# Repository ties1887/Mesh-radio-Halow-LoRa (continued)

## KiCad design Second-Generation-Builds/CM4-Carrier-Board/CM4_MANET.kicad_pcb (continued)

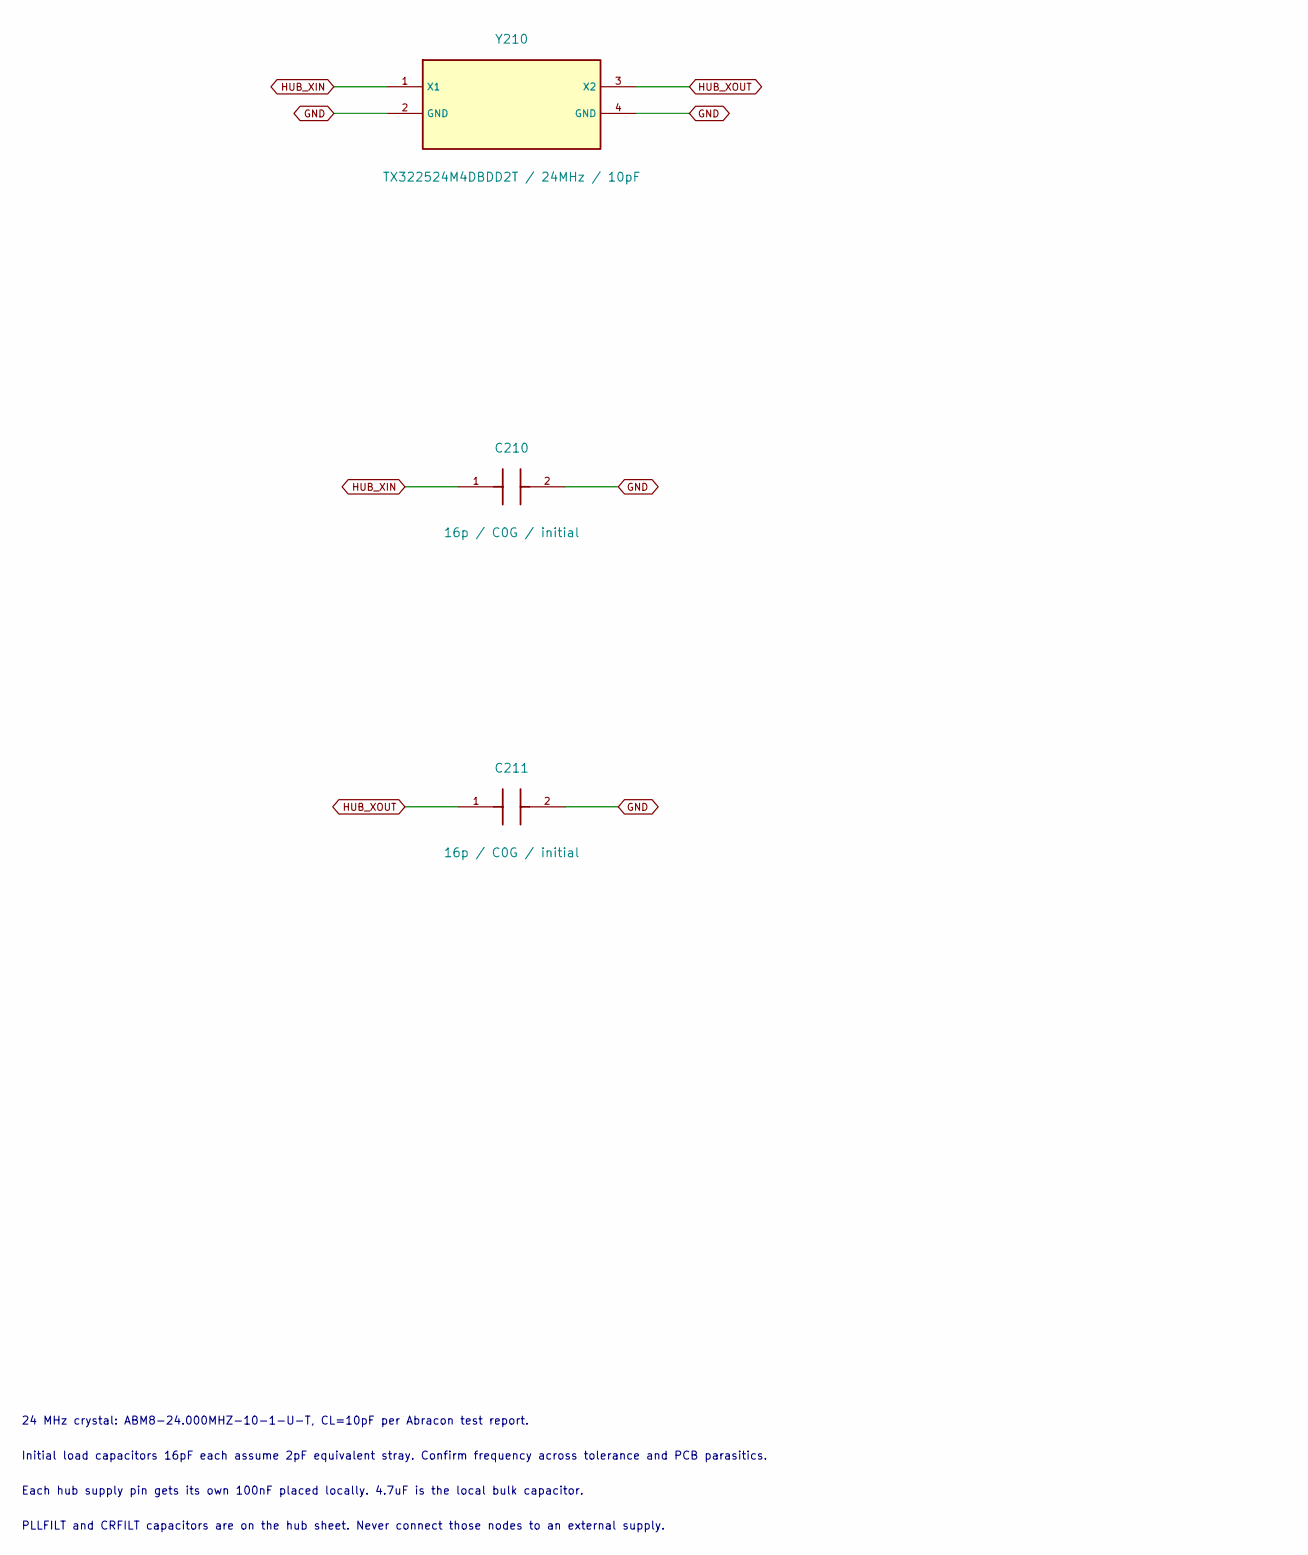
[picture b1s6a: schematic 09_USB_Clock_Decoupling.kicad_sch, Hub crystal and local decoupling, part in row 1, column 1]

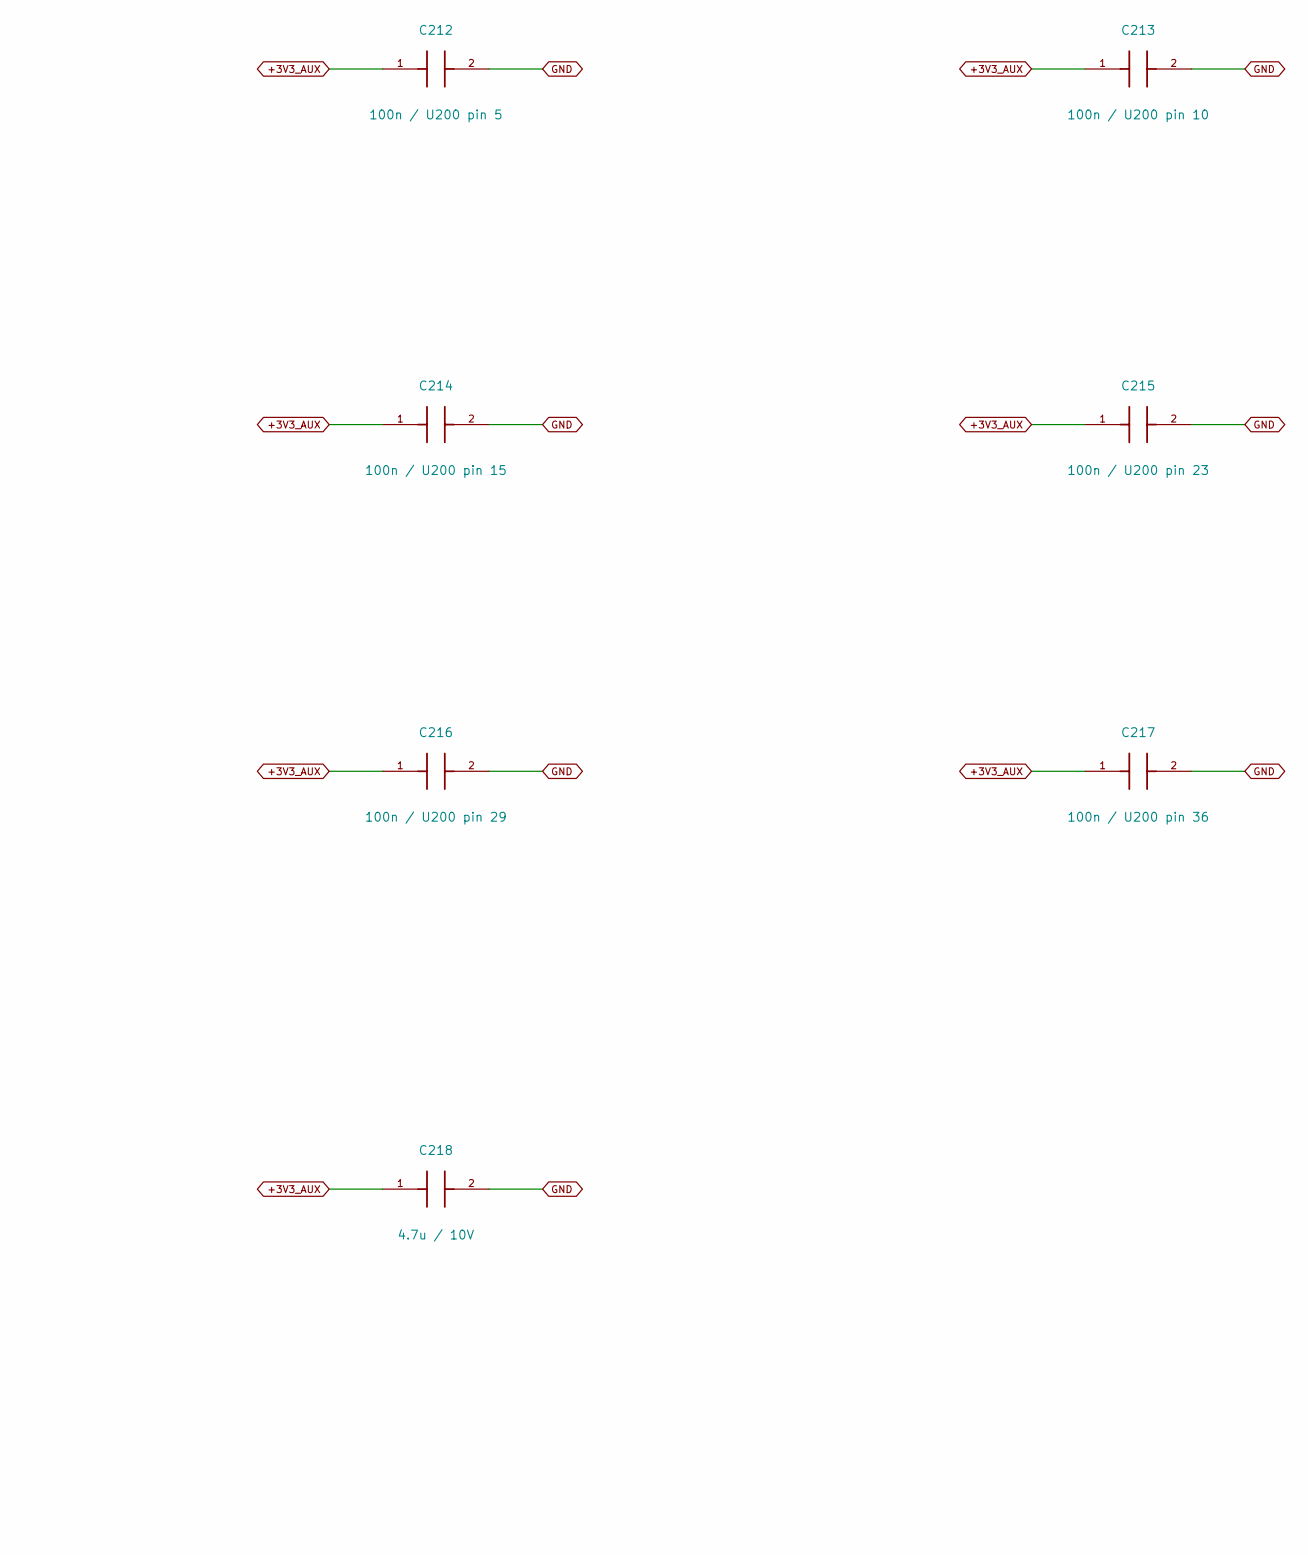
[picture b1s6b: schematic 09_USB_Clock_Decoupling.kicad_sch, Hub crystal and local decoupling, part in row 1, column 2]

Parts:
C210, C211: 16p / C0G / initial; C_0603_1608Metric; MPN CGA0603C0G160J500JT; LCSC C51704736
C212: 100n / U200 pin 5; C_0603_1608Metric; MPN CL10B104KB8NNNC; LCSC C1591
C213: 100n / U200 pin 10; C_0603_1608Metric; MPN CL10B104KB8NNNC; LCSC C1591
C214: 100n / U200 pin 15; C_0603_1608Metric; MPN CL10B104KB8NNNC; LCSC C1591
C215: 100n / U200 pin 23; C_0603_1608Metric; MPN CL10B104KB8NNNC; LCSC C1591
C216: 100n / U200 pin 29; C_0603_1608Metric; MPN CL10B104KB8NNNC; LCSC C1591
C217: 100n / U200 pin 36; C_0603_1608Metric; MPN CL10B104KB8NNNC; LCSC C1591
C218: 4.7u / 10V; C_0805_2012Metric; MPN C0805C475M8PACTU; LCSC C2175388
Y210: TX322524M4DBDD2T / 24MHz / 10pF; Crystal_SMD_3225-4Pin_3.2x2.5mm; MPN TX322524M4DBDD2T; LCSC C5308005

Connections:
+3V3_AUX: C212.1, C213.1, C214.1, C215.1, C216.1, C217.1, C218.1; also elsewhere on the board
GND: C210.2, C211.2, C212.2, C213.2, C214.2, C215.2, C216.2, C217.2, C218.2, Y210.2 (GND), Y210.4 (GND); also elsewhere on the board
HUB_XIN: C210.1, Y210.1 (X1); also elsewhere on the board
HUB_XOUT: C211.1, Y210.3 (X2); also elsewhere on the board

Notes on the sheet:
Initial load capacitors 16pF each assume 2pF equivalent stray. Confirm frequency across tolerance and PCB parasitics.
Each hub supply pin gets its own 100nF placed locally. 4.7uF is the local bulk capacitor.
24 MHz crystal: ABM8-24.000MHZ-10-1-U-T, CL=10pF per Abracon test report.
PLLFILT and CRFILT capacitors are on the hub sheet. Never connect those nodes to an external supply.

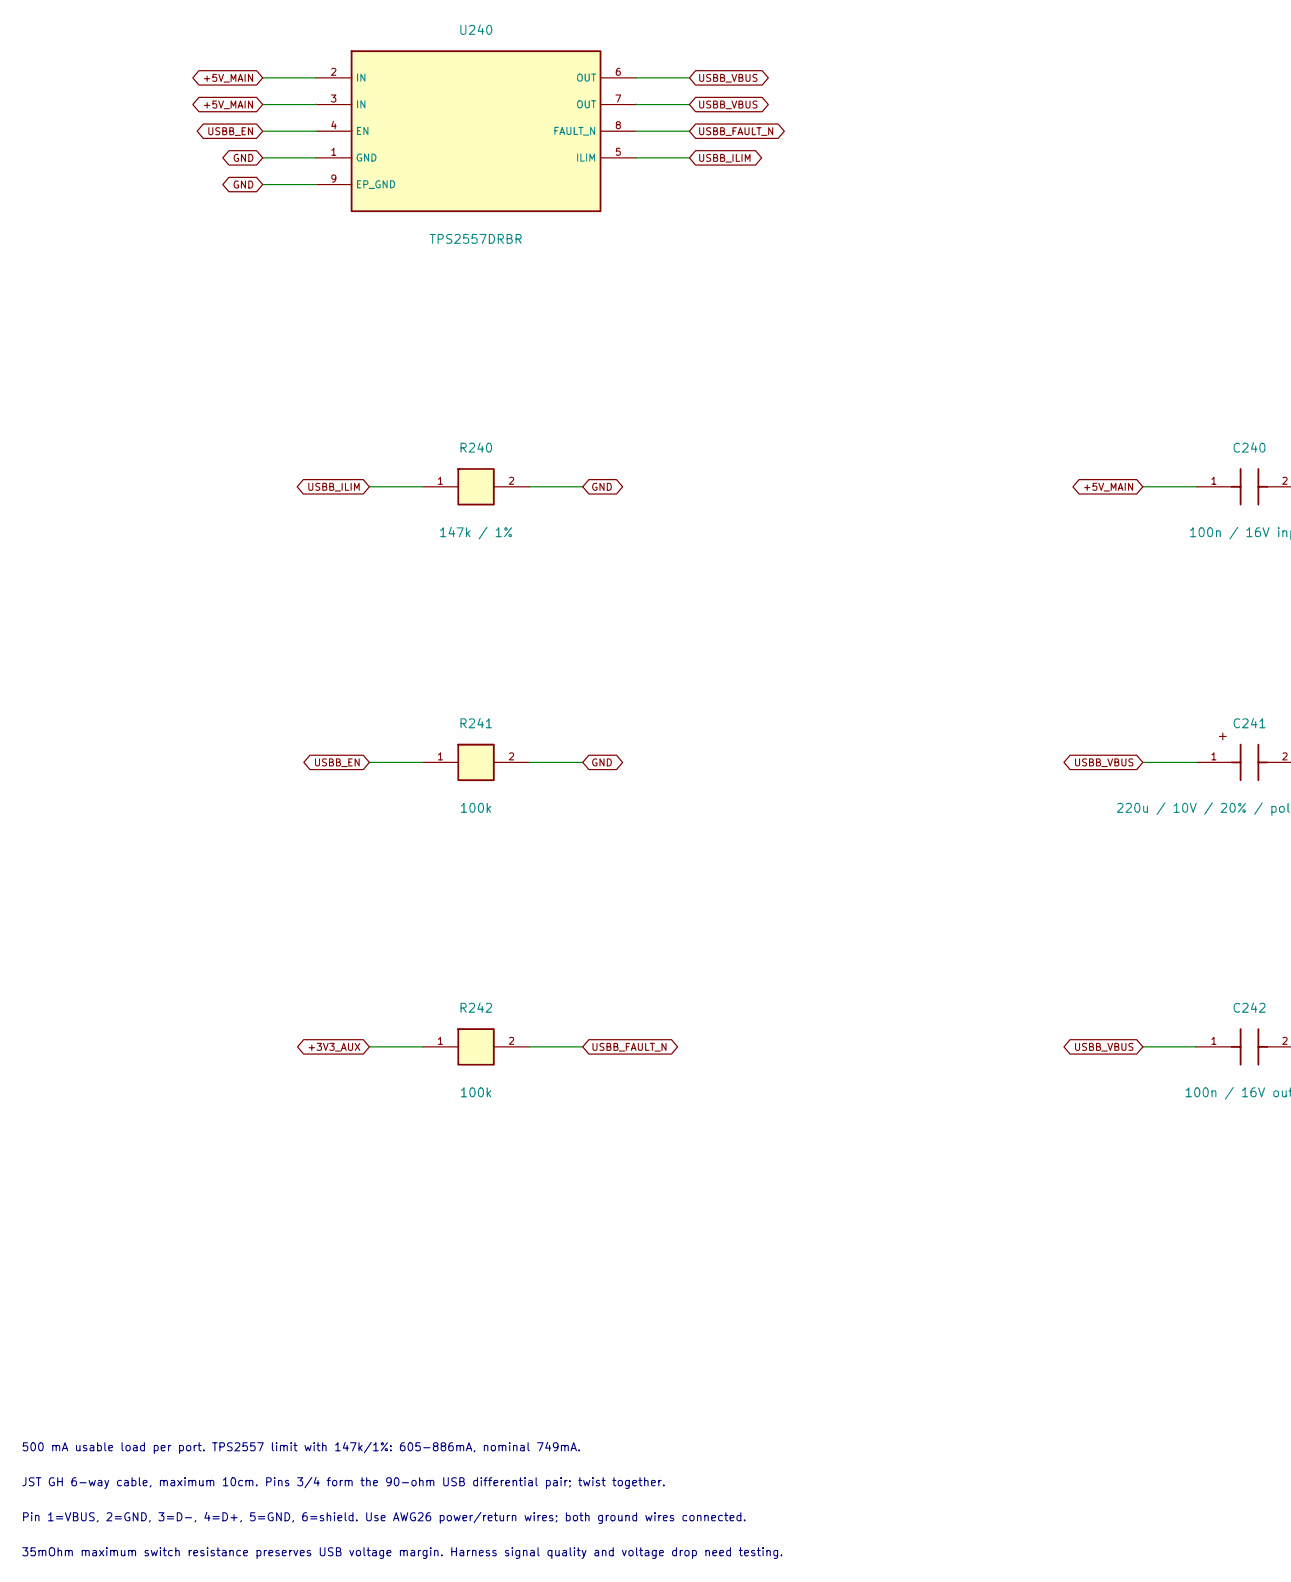
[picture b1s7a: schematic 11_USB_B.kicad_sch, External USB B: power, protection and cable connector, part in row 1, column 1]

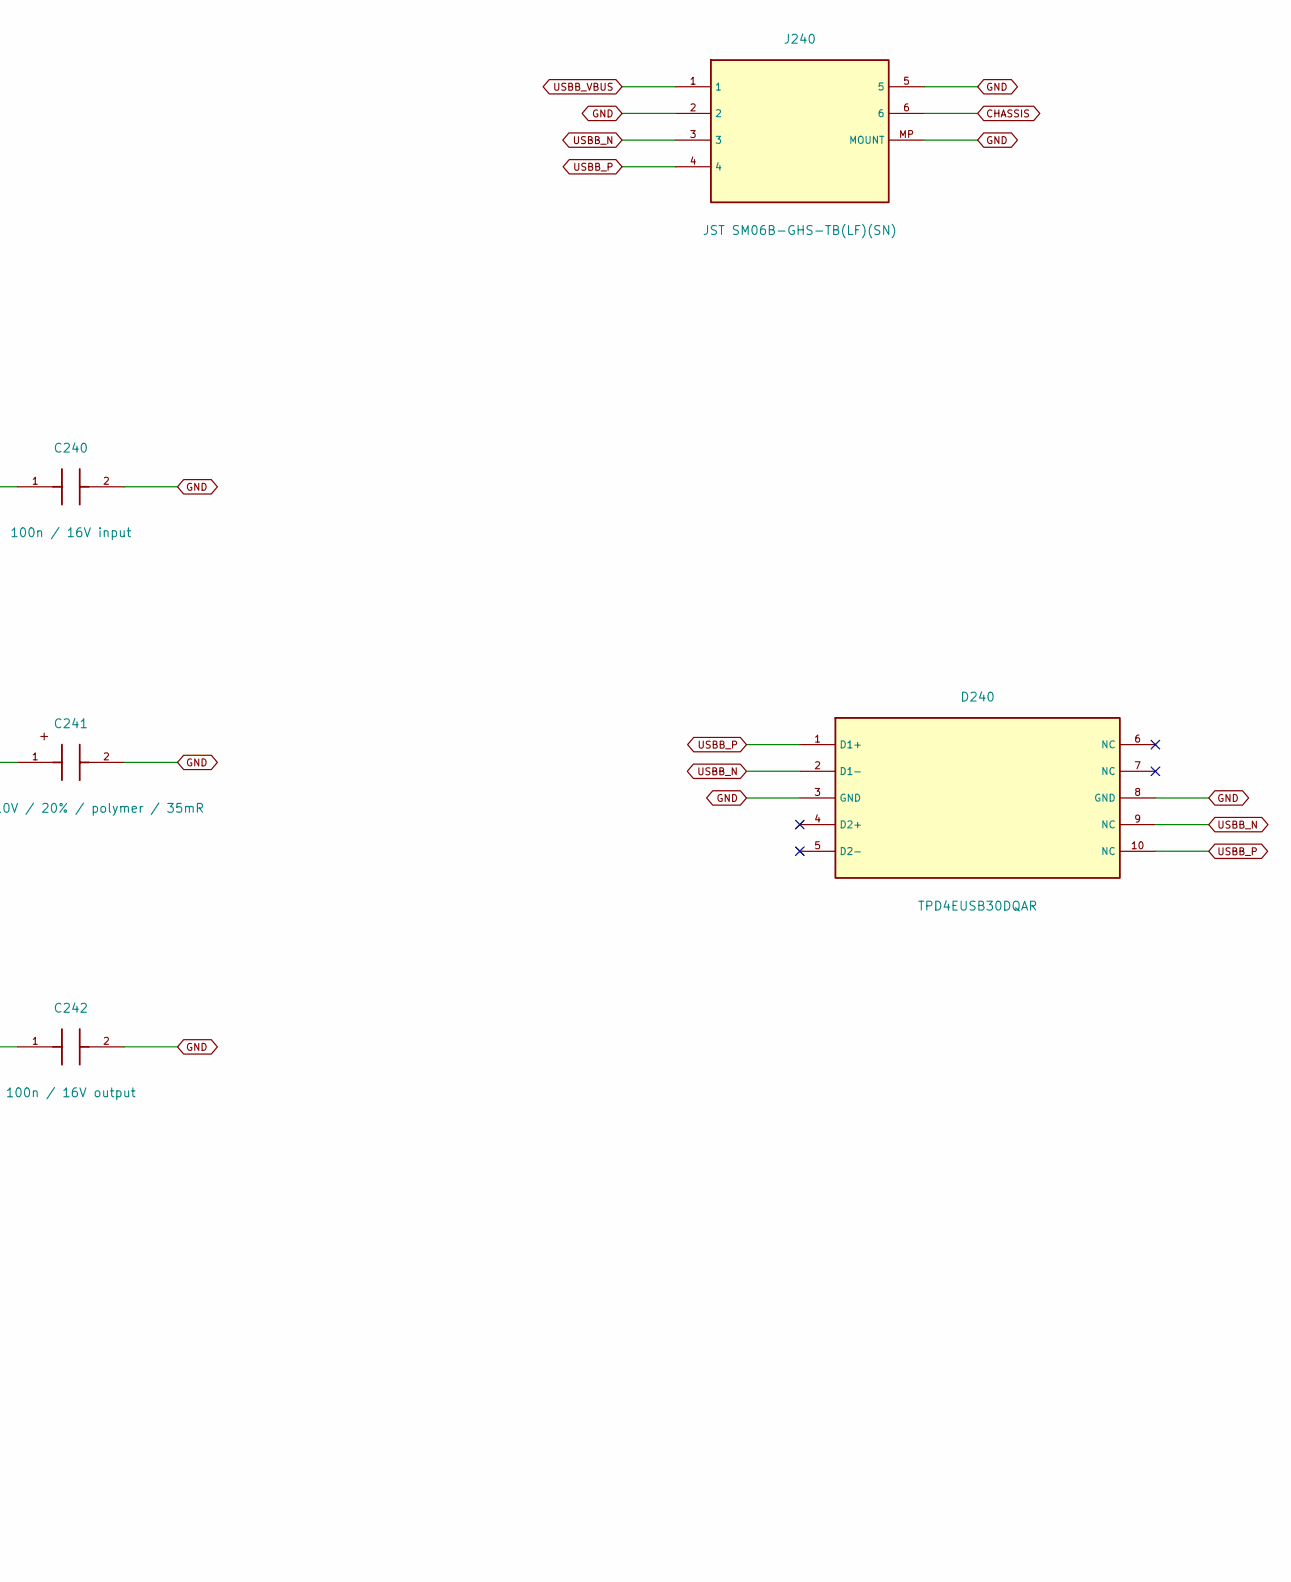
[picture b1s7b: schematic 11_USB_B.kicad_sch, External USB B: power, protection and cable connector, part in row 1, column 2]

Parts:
C240: 100n / 16V input; C_0603_1608Metric; MPN CL10B104KB8NNNC; LCSC C1591
C241: 220u / 10V / 20% / polymer / 35mR; CP_Elec_6.3x5.8; MPN JBLM2221M010C058RTM 220UF 10V; LCSC C19270700
C242: 100n / 16V output; C_0603_1608Metric; MPN CL10B104KB8NNNC; LCSC C1591
D240: TPD4EUSB30DQAR; USON-10_2.5x1.0mm_P0.5mm; MPN TPD4EUSB30DQAR; LCSC C90627
J240: JST SM06B-GHS-TB(LF)(SN); JST_GH_SM06B-GHS-TB_1x06-1MP_P1.25mm_Horizontal; MPN SM06B-GHS-TB(LF)(SN); LCSC C133065
R240: 147k / 1%; R_0603_1608Metric; MPN CR-03FL7---147K; LCSC C216852
R241, R242: 100k; R_0603_1608Metric; MPN 0603WAF1003T5E; LCSC C25803
U240: TPS2557DRBR; VSON-8-1EP_3x3mm_P0.65mm_EP1.65x2.4mm; MPN TPS2557DRBR; LCSC C130056

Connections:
+3V3_AUX: R242.1; also elsewhere on the board
+5V_MAIN: C240.1, U240.2 (IN), U240.3 (IN); also elsewhere on the board
CHASSIS: J240.6; also elsewhere on the board
GND: C240.2, C241.2, C242.2, D240.3 (GND), D240.8 (GND), J240.2, J240.5, J240.MP (MOUNT), R240.2, R241.2, U240.1 (GND), U240.9 (EP_GND); also elsewhere on the board
USBB_EN: R241.1, U240.4 (EN); also elsewhere on the board
USBB_FAULT_N: R242.2, U240.8 (FAULT_N); also elsewhere on the board
USBB_ILIM: R240.1, U240.5 (ILIM)
USBB_N: D240.2 (D1-), D240.9 (NC), J240.3; also elsewhere on the board
USBB_P: D240.1 (D1+), D240.10 (NC), J240.4; also elsewhere on the board
USBB_VBUS: C241.1, C242.1, J240.1, U240.6 (OUT), U240.7 (OUT)

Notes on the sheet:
Pin 1=VBUS, 2=GND, 3=D-, 4=D+, 5=GND, 6=shield. Use AWG26 power/return wires; both ground wires connected.
35mOhm maximum switch resistance preserves USB voltage margin. Harness signal quality and voltage drop need testing.
500 mA usable load per port. TPS2557 limit with 147k/1%: 605-886mA, nominal 749mA.
JST GH 6-way cable, maximum 10cm. Pins 3/4 form the 90-ohm USB differential pair; twist together.

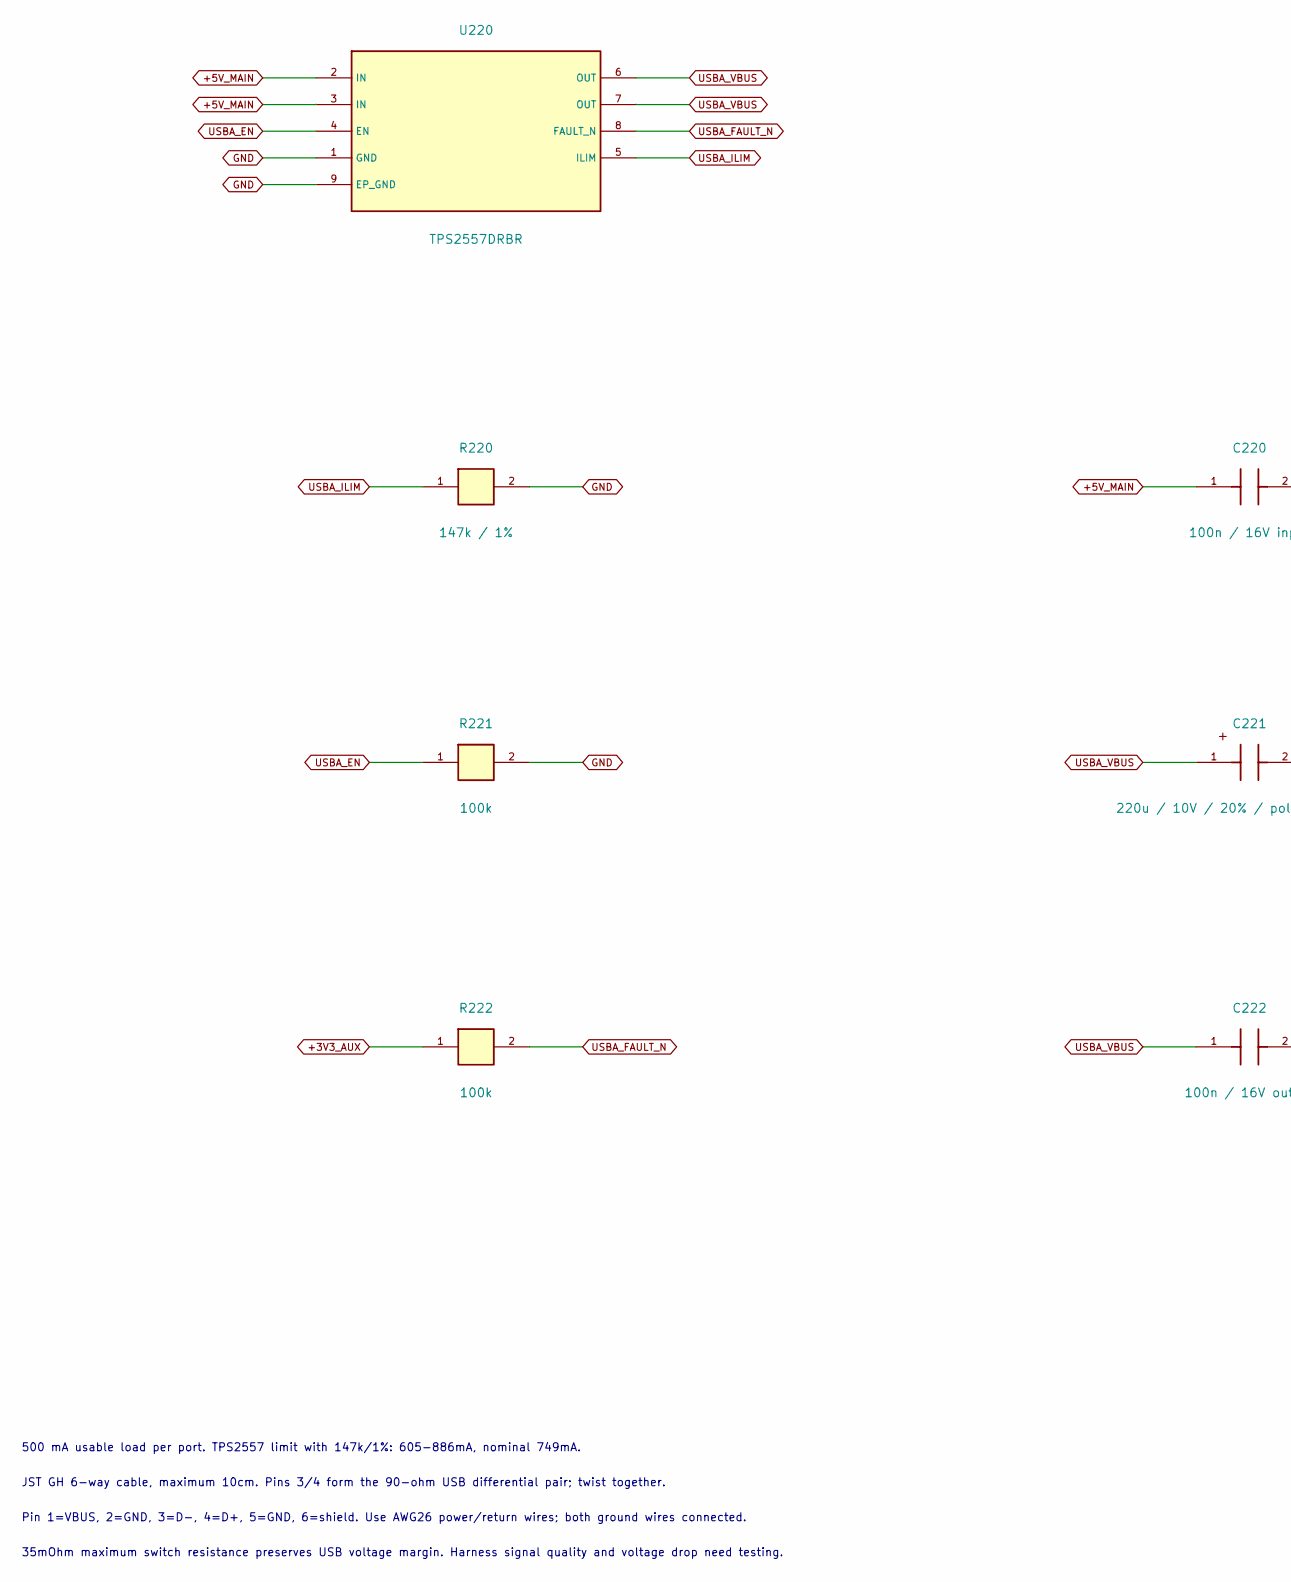
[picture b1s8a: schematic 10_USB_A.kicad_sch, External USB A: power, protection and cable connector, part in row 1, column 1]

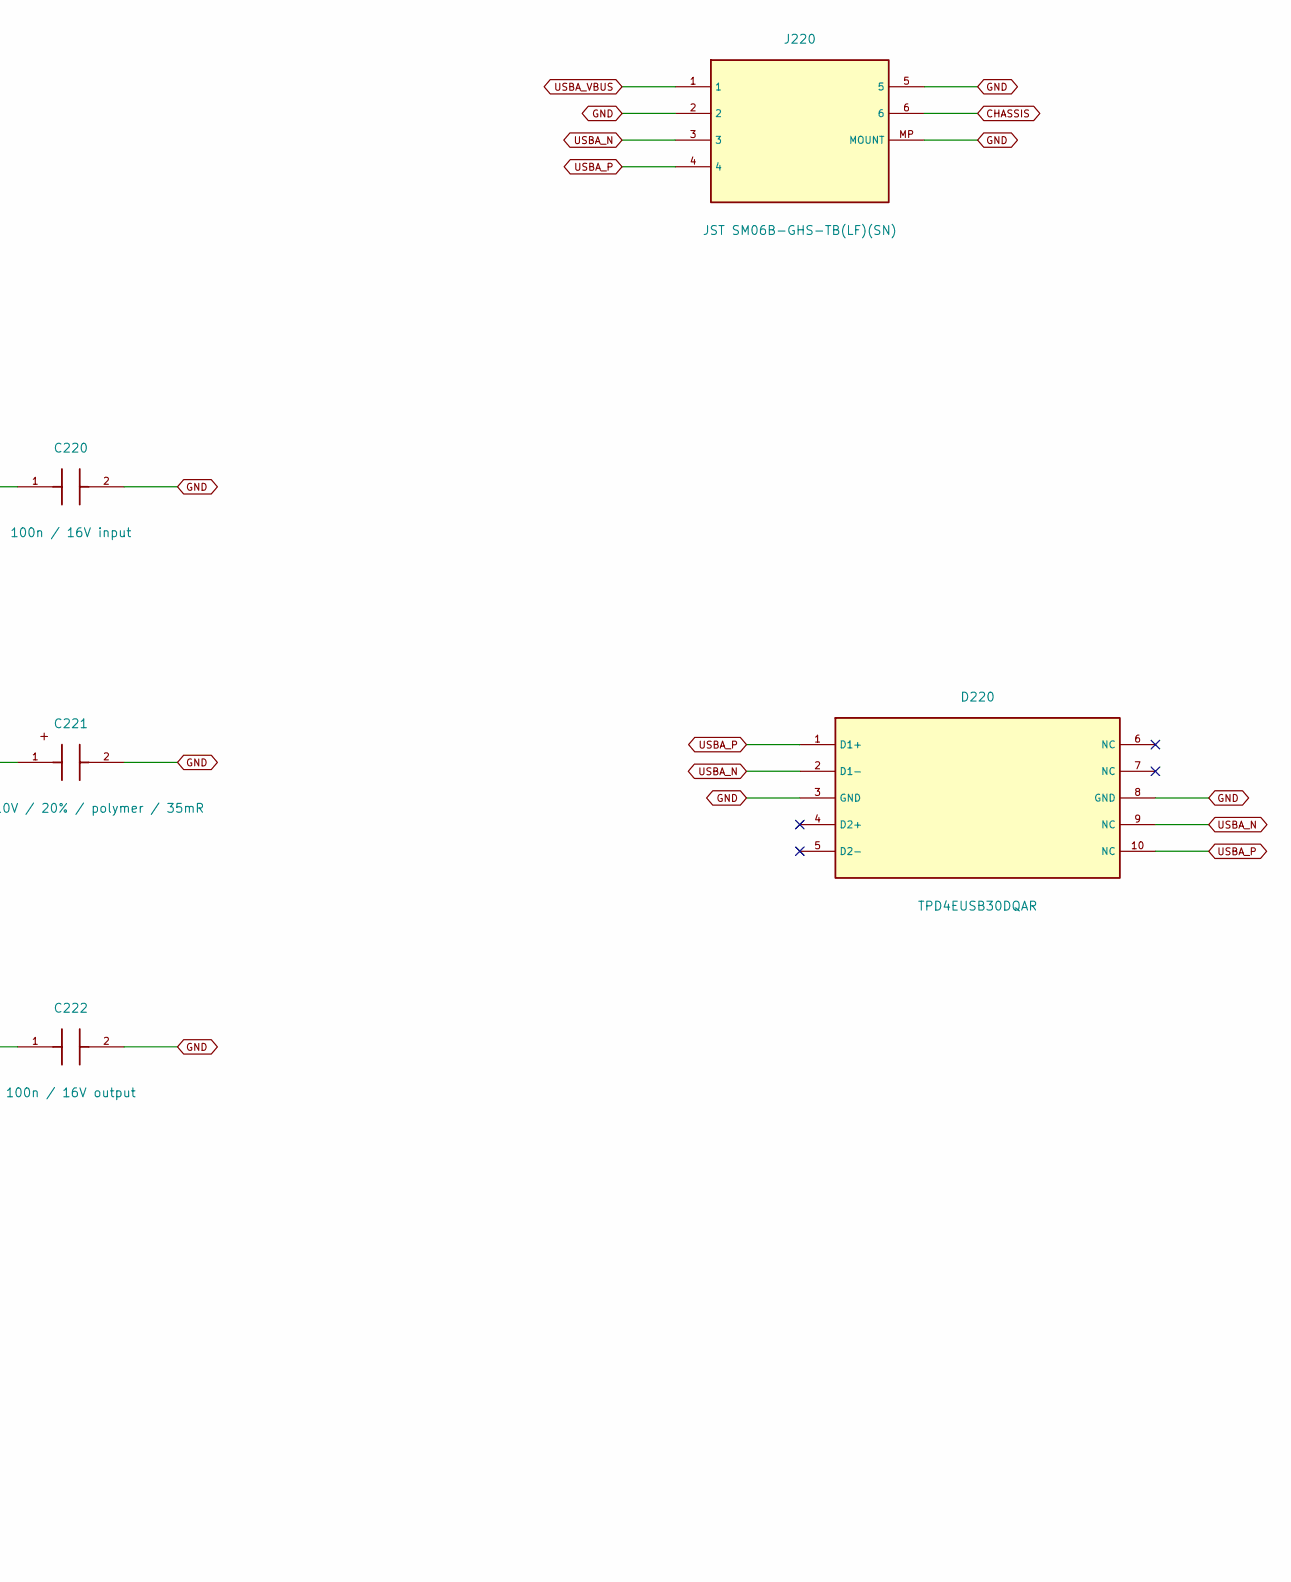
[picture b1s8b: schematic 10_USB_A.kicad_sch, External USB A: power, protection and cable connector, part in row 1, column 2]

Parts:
C220: 100n / 16V input; C_0603_1608Metric; MPN CL10B104KB8NNNC; LCSC C1591
C221: 220u / 10V / 20% / polymer / 35mR; CP_Elec_6.3x5.8; MPN JBLM2221M010C058RTM 220UF 10V; LCSC C19270700
C222: 100n / 16V output; C_0603_1608Metric; MPN CL10B104KB8NNNC; LCSC C1591
D220: TPD4EUSB30DQAR; USON-10_2.5x1.0mm_P0.5mm; MPN TPD4EUSB30DQAR; LCSC C90627
J220: JST SM06B-GHS-TB(LF)(SN); JST_GH_SM06B-GHS-TB_1x06-1MP_P1.25mm_Horizontal; MPN SM06B-GHS-TB(LF)(SN); LCSC C133065
R220: 147k / 1%; R_0603_1608Metric; MPN CR-03FL7---147K; LCSC C216852
R221, R222: 100k; R_0603_1608Metric; MPN 0603WAF1003T5E; LCSC C25803
U220: TPS2557DRBR; VSON-8-1EP_3x3mm_P0.65mm_EP1.65x2.4mm; MPN TPS2557DRBR; LCSC C130056

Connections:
+3V3_AUX: R222.1; also elsewhere on the board
+5V_MAIN: C220.1, U220.2 (IN), U220.3 (IN); also elsewhere on the board
CHASSIS: J220.6; also elsewhere on the board
GND: C220.2, C221.2, C222.2, D220.3 (GND), D220.8 (GND), J220.2, J220.5, J220.MP (MOUNT), R220.2, R221.2, U220.1 (GND), U220.9 (EP_GND); also elsewhere on the board
USBA_EN: R221.1, U220.4 (EN); also elsewhere on the board
USBA_FAULT_N: R222.2, U220.8 (FAULT_N); also elsewhere on the board
USBA_ILIM: R220.1, U220.5 (ILIM)
USBA_N: D220.2 (D1-), D220.9 (NC), J220.3; also elsewhere on the board
USBA_P: D220.1 (D1+), D220.10 (NC), J220.4; also elsewhere on the board
USBA_VBUS: C221.1, C222.1, J220.1, U220.6 (OUT), U220.7 (OUT)

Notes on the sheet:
35mOhm maximum switch resistance preserves USB voltage margin. Harness signal quality and voltage drop need testing.
500 mA usable load per port. TPS2557 limit with 147k/1%: 605-886mA, nominal 749mA.
JST GH 6-way cable, maximum 10cm. Pins 3/4 form the 90-ohm USB differential pair; twist together.
Pin 1=VBUS, 2=GND, 3=D-, 4=D+, 5=GND, 6=shield. Use AWG26 power/return wires; both ground wires connected.

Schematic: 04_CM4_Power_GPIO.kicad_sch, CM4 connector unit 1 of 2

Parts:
U100: CM4 Lite / 4GB / no WiFi; Raspberry-Pi-4-Compute-Module; JLCPCB Status EXCLUDE_FROM_JLCPCB_ASSEMBLY

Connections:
+3V3_CM4: U100.78 (GPIO_VREF(1.8v/3.3v_Input)), U100.84 (+3.3v_(Output)), U100.86 (+3.3v_(Output)); also elsewhere on the board
+5V_MAIN: U100.77 (+5v_(Input)), U100.79 (+5v_(Input)), U100.81 (+5v_(Input)), U100.83 (+5v_(Input)), U100.85 (+5v_(Input)), U100.87 (+5v_(Input)); also elsewhere on the board
CM4_GLOBAL_EN: U100.99 (Global_EN); also elsewhere on the board
CM4_nEXTRST: U100.100 (nEXTRST); also elsewhere on the board
CM4_nRPIBOOT: U100.93 (nRPIBOOT); also elsewhere on the board
ETH0_N: U100.10 (Ethernet_Pair0_N); also elsewhere on the board
ETH0_P: U100.12 (Ethernet_Pair0_P); also elsewhere on the board
ETH1_N: U100.6 (Ethernet_Pair1_N); also elsewhere on the board
ETH1_P: U100.4 (Ethernet_Pair1_P); also elsewhere on the board
ETH2_N: U100.9 (Ethernet_Pair2_N); also elsewhere on the board
ETH2_P: U100.11 (Ethernet_Pair2_P); also elsewhere on the board
ETH3_N: U100.5 (Ethernet_Pair3_N); also elsewhere on the board
ETH3_P: U100.3 (Ethernet_Pair3_P); also elsewhere on the board
GND: U100.1 (GND), U100.7 (GND), U100.8 (GND), U100.13 (GND), U100.14 (GND), U100.22 (GND), U100.23 (GND), U100.32 (GND), U100.33 (GND), U100.42 (GND), U100.43 (GND), U100.52 (GND), U100.53 (GND), U100.59 (GND), U100.60 (GND), U100.65 (GND), U100.66 (GND), U100.71 (GND), U100.74 (GND), U100.98 (GND); also elsewhere on the board
SD_CLK: U100.57 (SD_CLK); also elsewhere on the board
SD_CMD: U100.62 (SD_CMD); also elsewhere on the board
SD_DAT0: U100.63 (SD_DAT0); also elsewhere on the board
SD_DAT1: U100.67 (SD_DAT1); also elsewhere on the board
SD_DAT2: U100.69 (SD_DAT2); also elsewhere on the board
SD_DAT3: U100.61 (SD_DAT3); also elsewhere on the board
SD_PWR_ON: U100.75 (SD_PWR_ON); also elsewhere on the board
UART_RXD: U100.51 (GPIO15); also elsewhere on the board
UART_TXD: U100.55 (GPIO14); also elsewhere on the board

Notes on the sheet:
CM4 Lite 4 GB without WiFi; microSD is required. GPIO_VREF is supplied from CM4 own 3.3 V output.
Unused functions explicitly not connected. All ground and 5 V contacts connected.
One physical CM4 footprint containing both 100-pin connectors. Pin numbers from official Raspberry Pi CM4IO.

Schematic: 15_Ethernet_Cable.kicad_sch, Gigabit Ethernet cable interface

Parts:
C500: 1n / 2kV / X7R / shield coupling; C_1812_4532Metric; MPN 1812B102K202NT; LCSC C36077
C501: 100n; C_0402_1005Metric; MPN GRM155R71C104KA88J; LCSC C106994
C502: 1n / 2kV; C_1812_4532Metric; MPN 1812B102K202NT; LCSC C36077
D500, D501: TPD4EUSB30DQAR; USON-10_2.5x1.0mm_P0.5mm; MPN TPD4EUSB30DQAR; LCSC C90627
J500: JST SM12B-GHS-TB(LF)(SN); JST_GH_SM12B-GHS-TB_1x12-1MP_P1.25mm_Horizontal; MPN SM12B-GHS-TB(LF)(SN); LCSC C265421
R500: 1M / shield bleed; R_0603_1608Metric; MPN 0603WAF1004T5E; LCSC C22935
R501: 0R / optional chassis bond; R_0603_1608Metric; JLCPCB Status EXCLUDE_FROM_JLCPCB_ASSEMBLY; not fitted
R502, R503, R504, R505: 75R; R_0603_1608Metric; MPN RC0603FR-0775RL; LCSC C112309
T500: G2401CE / C2904710; SMD-24_L15.1-W7.1-P1.00-LS10.0-BL

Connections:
CHASSIS: C500.1, C502.2, J500.12, R500.1, R501.1; also elsewhere on the board
ETH0_N: D500.2 (D1-), T500.3; also elsewhere on the board
ETH0_P: D500.1 (D1+), T500.2; also elsewhere on the board
ETH1_N: D500.5 (D2-), T500.6; also elsewhere on the board
ETH1_P: D500.4 (D2+), T500.5; also elsewhere on the board
ETH2_N: D501.2 (D1-), T500.9; also elsewhere on the board
ETH2_P: D501.1 (D1+), T500.8; also elsewhere on the board
ETH3_N: D501.5 (D2-), T500.12; also elsewhere on the board
ETH3_P: D501.4 (D2+), T500.11; also elsewhere on the board
ETH_BST: C502.1, R502.2, R503.2, R504.2, R505.2
ETH_C0_CT: R502.1, T500.24
ETH_C0_N: J500.3, T500.22
ETH_C0_P: J500.2, T500.23
ETH_C1_CT: R503.1, T500.21
ETH_C1_N: J500.5, T500.19
ETH_C1_P: J500.4, T500.20
ETH_C2_CT: R504.1, T500.18
ETH_C2_N: J500.8, T500.16
ETH_C2_P: J500.7, T500.17
ETH_C3_CT: R505.1, T500.15
ETH_C3_N: J500.10, T500.13
ETH_C3_P: J500.9, T500.14
ETH_PHY_CT: C501.1, T500.1, T500.4, T500.7, T500.10
GND: C500.2, C501.2, D500.3 (GND), D500.8 (GND), D501.3 (GND), D501.8 (GND), J500.1, J500.6, J500.11, J500.MP (MOUNT), R500.2, R501.2; also elsewhere on the board

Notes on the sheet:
No Ethernet transformer on carrier. External assembly must contain the specified magnetics; plain RJ45 alone will not work.
Pinout: 1 GND, 2/3 pair0 +/-, 4/5 pair1 +/-, 6 GND, 7/8 pair2 +/-, 9/10 pair3 +/-, 11 GND, 12 shield.
JST GH 12-way is a prototype candidate: four 100-ohm twisted pairs, short untwisted ends, shielded cable.
RJ45/MagJack is on enclosure panel, not on carrier. Maximum internal cable length 10cm.

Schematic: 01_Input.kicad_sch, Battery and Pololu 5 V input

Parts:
C1: 47u / 16V / X6S; C_1210_3225Metric; MPN GRM32EC81C476KE15L; LCSC C162512
C2: 100n / 16V / X7R; C_0603_1608Metric; MPN CL10B104KB8NNNC; LCSC C1591
J1: BATTERY SOLDER PADS; Battery_Pads; JLCPCB Status EXCLUDE_FROM_JLCPCB_ASSEMBLY
PS1: Pololu #5571 / D42V55F5; Pololu_D42V55F5; JLCPCB Status EXCLUDE_FROM_JLCPCB_ASSEMBLY
R1: 100k / 1%; R_0603_1608Metric; MPN 0603WAF1003T5E; LCSC C25803
TP1: +5V_MAIN; TestPoint_Pad_D1.5mm; JLCPCB Status EXCLUDE_FROM_JLCPCB_ASSEMBLY
TP2: GND; TestPoint_Pad_D1.5mm; JLCPCB Status EXCLUDE_FROM_JLCPCB_ASSEMBLY
TP3: MAIN_PG; TestPoint_Pad_D1.5mm; JLCPCB Status EXCLUDE_FROM_JLCPCB_ASSEMBLY

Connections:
+5V_MAIN: C1.1, C2.1, PS1.VOUT (VOUT_5V), R1.1, TP1.1; also elsewhere on the board
BAT_POS: J1.1, PS1.VIN
GND: C1.2, C2.2, J1.2, PS1.GND, TP2.1; also elsewhere on the board
MAIN_PG: PS1.PG, R1.2, TP3.1

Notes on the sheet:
Total 5 V budget remains near the regulator capability; thermal/load qualification is mandatory.
Pololu EN is pulled to battery VIN internally: do not connect directly to CM4 GPIO.
Pololu duplicated power pads share names. Manual assembly with clearance above carrier required.
Battery: 2S-4S, normally 3S. Two solder pads only. Pololu solder-mounted on carrier.

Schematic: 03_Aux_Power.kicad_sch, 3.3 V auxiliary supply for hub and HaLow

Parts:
C20: 10u / 10V; C_0805_2012Metric; MPN CL21A106KAYNNNE; LCSC C15850
C21: 100n / 16V AVIN; C_0603_1608Metric; MPN CL10B104KB8NNNC; LCSC C1591
C22: 22u / 10V; C_1206_3216Metric; MPN 1206X226K160NT; LCSC C105480
C23: 10n / 16V SS; C_0603_1608Metric; MPN TCC0603X7R103M500CT; LCSC C376807
L20: 2.2u / XFL4020-222MEC; L_Coilcraft_XxL4020; MPN XFL4020-222MEC; LCSC C122469
TP20: +3V3_AUX; TestPoint_Pad_D1.5mm; JLCPCB Status EXCLUDE_FROM_JLCPCB_ASSEMBLY
U20: TPS62142RGTR; VQFN-16-1EP_3x3mm_P0.5mm_EP1.68x1.68mm; MPN TPS62142RGTR; LCSC C129331

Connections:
+3V3_AUX: C22.1, L20.2, TP20.1, U20.14 (VOS); also elsewhere on the board
+5V_MAIN: C20.1, C21.1, U20.10 (AVIN), U20.11 (PVIN), U20.12 (PVIN), U20.13 (EN); also elsewhere on the board
AUX_SS: C23.1, U20.9 (SS_TR)
AUX_SW: L20.1, U20.1 (SW), U20.2 (SW), U20.3 (SW)
GND: C20.2, C21.2, C22.2, C23.2, U20.5 (FB_FIXED_GND), U20.6 (AGND), U20.7 (FSW), U20.8 (DEF), U20.15 (PGND), U20.16 (PGND), U20.17 (EP_GND); also elsewhere on the board
HUB_RESET_N: U20.4 (PG); also elsewhere on the board

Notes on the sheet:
TPS62142 fixed 3.3 V / 2 A. CM4 3.3 V output is a separate rail; never join the two.
FSW=GND selects nominal 2.5 MHz; DEF=GND selects nominal 3.3 V. FB grounded for fixed-output device.
SS/TR=10nF; nominal soft start about 5ms. Power-good joins open-drain hub reset interlock.
Coil/capacitor effective values and cumulative HaLow decoupling need transient validation.

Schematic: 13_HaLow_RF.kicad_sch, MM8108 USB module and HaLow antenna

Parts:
C300: 2.2u / 10V; C_0603_1608Metric; MPN CL10A225KO8NNNC; LCSC C23630
C301: 10u / 10V VBAT pin10; C_0805_2012Metric; MPN CL21A106KAYNNNE; LCSC C15850
C302: 10u / 10V VBAT_TX pin24; C_0805_2012Metric; MPN CL21A106KAYNNNE; LCSC C15850
C303: 10u / 10V VDD_USB pin25; C_0805_2012Metric; MPN CL21A106KAYNNNE; LCSC C15850
C304: 100n / 16V VDDIO pin22; C_0603_1608Metric; MPN CL10B104KB8NNNC; LCSC C1591
C305, C306: DNP / matching; C_0402_1005Metric; JLCPCB Status EXCLUDE_FROM_JLCPCB_ASSEMBLY; not fitted
C307, C308, C309: 100n / 16V / local MM8108 bypass; C_0603_1608Metric; MPN CL10B104KB8NNNC; LCSC C1591
J300: Hirose U.FL-R-SMT-1; U.FL_Hirose_U.FL-R-SMT-1_Vertical; MPN U.FL-R-SMT-1(80); LCSC C88374
R300: 220k / 1%; R_0603_1608Metric; MPN FRC0603F2203TS; LCSC C2907013
R301: 0R / RF link; R_0402_1005Metric; MPN 0402WGF0000TCE; LCSC C17168
U300: MM8108-MF15457; MorseMicro_MM8108-MF15457; MPN MM8108-MF15457; LCSC C51941506

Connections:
+3V3_HALOW: C301.1, C302.1, C303.1, C304.1, C307.1, C308.1, C309.1, R300.1, U300.10 (VBAT), U300.22 (VDDIO), U300.24 (VBAT_TX), U300.25 (VDD_USB); also elsewhere on the board
GND: C300.2, C301.2, C302.2, C303.2, C304.2, C305.2, C306.2, C307.2, C308.2, C309.2, J300.2 (GND), U300.1 (GND), U300.3 (GND), U300.11 (GND), U300.20 (GND), U300.23 (GND), U300.26 (GND), U300.30 (GND), U300.38 (GND); also elsewhere on the board
HALOW_ANT: C306.1, J300.1 (RF), R301.2
HALOW_RESET_N: C300.1, R300.2, U300.4 (RESET_N)
HALOW_RF: C305.1, R301.1, U300.2 (ANT)
HALOW_USB_N: U300.27 (USB_D_N); also elsewhere on the board
HALOW_USB_P: U300.28 (USB_D_P); also elsewhere on the board

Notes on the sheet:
R300/C300 provide reset delay. Matching network: 0R series fitted, both shunt capacitors DNP.
ANT to U.FL: short 50-ohm RF route with ground stitching. Exact module footprint and land pattern still require review.
USB pins 27/28. All four supply pins use switched 3.3 V. Unused SDIO/JTAG/GPIO pins left open as reference.
USB network adapter circuit based on Morse Micro MM8108-MF15457 datasheet v4 figure 4.

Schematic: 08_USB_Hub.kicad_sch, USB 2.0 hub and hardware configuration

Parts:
C200: 100n / 10V / low-ESR / CRFILT; C_0603_1608Metric; MPN CL10B104KB8NNNC; LCSC C1591
C201: 100n / 10V / low-ESR / PLLFILT; C_0603_1608Metric; MPN CL10B104KB8NNNC; LCSC C1591
R200: 12k / 1%; R_0603_1608Metric; MPN FRC0603F1202TS; LCSC C2906989
R201, R202, R203, R204, R205, R206: 10k; R_0603_1608Metric; MPN 0603WAF1002T5E; LCSC C25804
U200: USB2514B-AEZC-TR; QFN-36-1EP_6x6mm_P0.5mm_EP4.1x4.1mm; MPN USB2514B-AEZC-TR; LCSC C16251

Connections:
+3V3_AUX: R204.1, R205.1, R206.1, U200.5 (VDDA33), U200.10 (VDDA33), U200.15 (VDD33), U200.23 (VDD33), U200.29 (VDDA33), U200.36 (VDDA33); also elsewhere on the board
+3V3_CM4: U200.27 (VBUS_DET); also elsewhere on the board
GND: C200.2, C201.2, R200.2, R201.2, R202.2, R203.2, U200.11 (TEST), U200.37 (VSS); also elsewhere on the board
HALOW_EN: U200.12 (PRTPWR1/BC_EN1); also elsewhere on the board
HALOW_FAULT_N: U200.13 (OCS_N1); also elsewhere on the board
HALOW_USB_N: U200.1 (USBDM_DN1/PRT_DIS_M1); also elsewhere on the board
HALOW_USB_P: U200.2 (USBDP_DN1/PRT_DIS_P1); also elsewhere on the board
HUB_CFG0: R201.1, U200.24 (SCL/SMBCLK/CFG_SEL0)
HUB_CFG1: R202.1, U200.25 (HS_IND/CFG_SEL1)
HUB_CRFILT: C200.1, U200.14 (CRFILT)
HUB_NONREM0: R204.2, U200.28 (SUSP_IND/LOCAL_PWR/NON_REM0)
HUB_NONREM1: R203.1, U200.22 (SDA/SMBDATA/NON_REM1)
HUB_P4_N: R205.2, U200.8 (USBDM_DN4/PRT_DIS_M4)
HUB_P4_P: R206.2, U200.9 (USBDP_DN4/PRT_DIS_P4)
HUB_PLLFILT: C201.1, U200.34 (PLLFILT)
HUB_RBIAS: R200.1, U200.35 (RBIAS)
HUB_RESET_N: U200.26 (RESET_N); also elsewhere on the board
HUB_UP_N: U200.30 (USBDM_UP); also elsewhere on the board
HUB_UP_P: U200.31 (USBDP_UP); also elsewhere on the board
HUB_XIN: U200.33 (XTALIN/CLKIN); also elsewhere on the board
HUB_XOUT: U200.32 (XTALOUT); also elsewhere on the board
USBA_EN: U200.16 (PRTPWR2/BC_EN2); also elsewhere on the board
USBA_FAULT_N: U200.17 (OCS_N2); also elsewhere on the board
USBA_N: U200.3 (USBDM_DN2/PRT_DIS_M2); also elsewhere on the board
USBA_P: U200.4 (USBDP_DN2/PRT_DIS_P2); also elsewhere on the board
USBB_EN: U200.18 (PRTPWR3/BC_EN3); also elsewhere on the board
USBB_FAULT_N: U200.19 (OCS_N3); also elsewhere on the board
USBB_N: U200.6 (USBDM_DN3/PRT_DIS_M3); also elsewhere on the board
USBB_P: U200.7 (USBDP_DN3/PRT_DIS_P3); also elsewhere on the board

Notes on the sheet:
VBUS_DET references the host CM4 3.3 V rail. HUB_RESET_N also depends on CM4 startup and AUX power-good.
CFG_SEL[1:0]=00: self-powered, individual switching and current sensing (datasheet table 5-1).
NON_REM[1:0]=01: only port 1 non-removable. Disabled port 4 has both data pins pulled up.
USB2514B: physical port 1=internal HaLow; ports 2/3=external USB A/B; port 4 disabled.
